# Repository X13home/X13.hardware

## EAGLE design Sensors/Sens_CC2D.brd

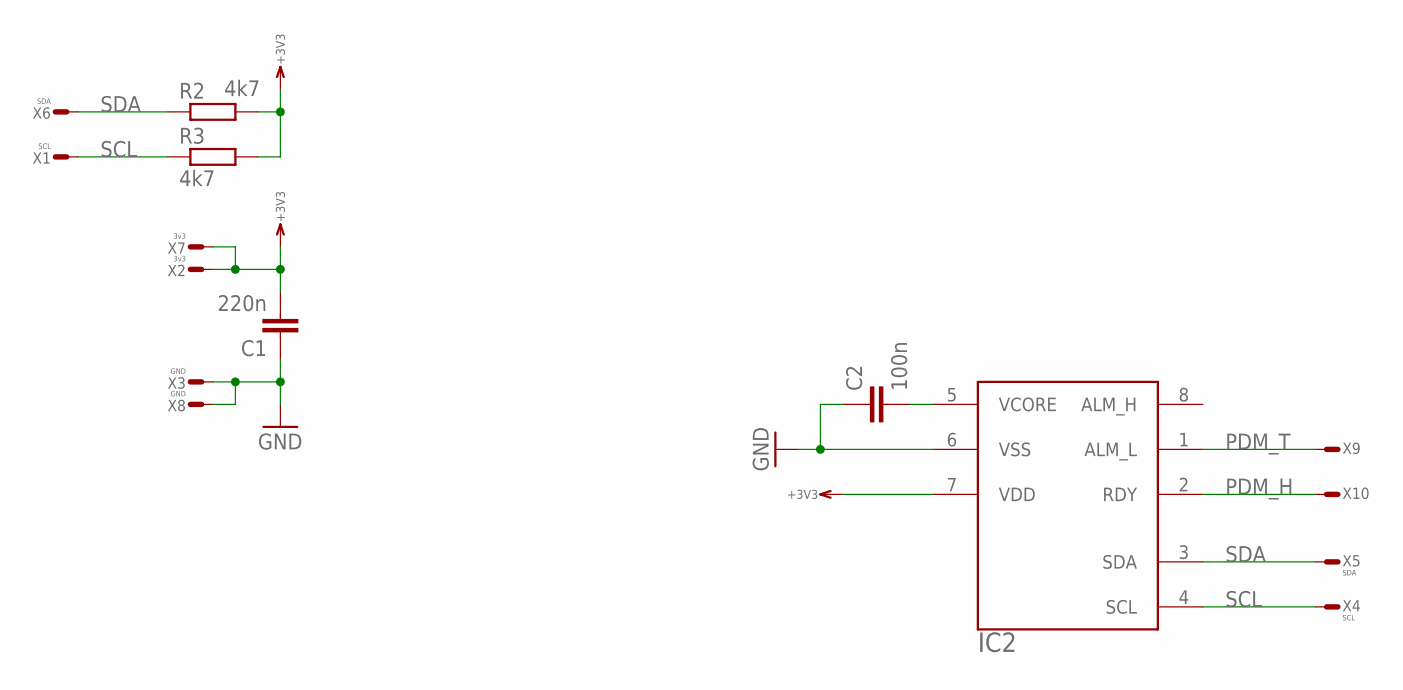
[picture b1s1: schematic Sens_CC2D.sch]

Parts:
C1: 220n; 0603
C2: 100n; 0603
IC2: CC2D
R2, R3: 4k7; 0603
X1, X4: SCL; T1.6/0.9
X2, X7: 3v3; T1.6/0.9
X3, X8: GND; T1.6/0.9
X5, X6: SDA; T1.6/0.9
X9, X10: WIREPADR; S1.27R

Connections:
+3V3: C1.2, IC2.7 (VDD), R2.2, R3.2, X2.1, X7.1
GND: C1.1, C2.1, IC2.6 (VSS), X3.1, X8.1
unnamed: C2.2, IC2.5 (VCORE)
PDM_H: IC2.2 (RDY), X10.1
PDM_T: IC2.1 (ALM_L), X9.1
SCL: IC2.4 (SCL), R3.1, X1.1, X4.1
SDA: IC2.3 (SDA), R2.1, X5.1, X6.1

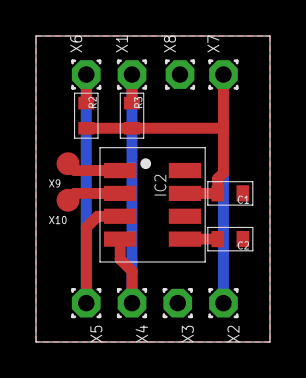
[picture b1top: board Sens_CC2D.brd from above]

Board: 2 copper layers, 13.0 x 17.0 mm, 15 parts (0 on the bottom side), 7 nets.

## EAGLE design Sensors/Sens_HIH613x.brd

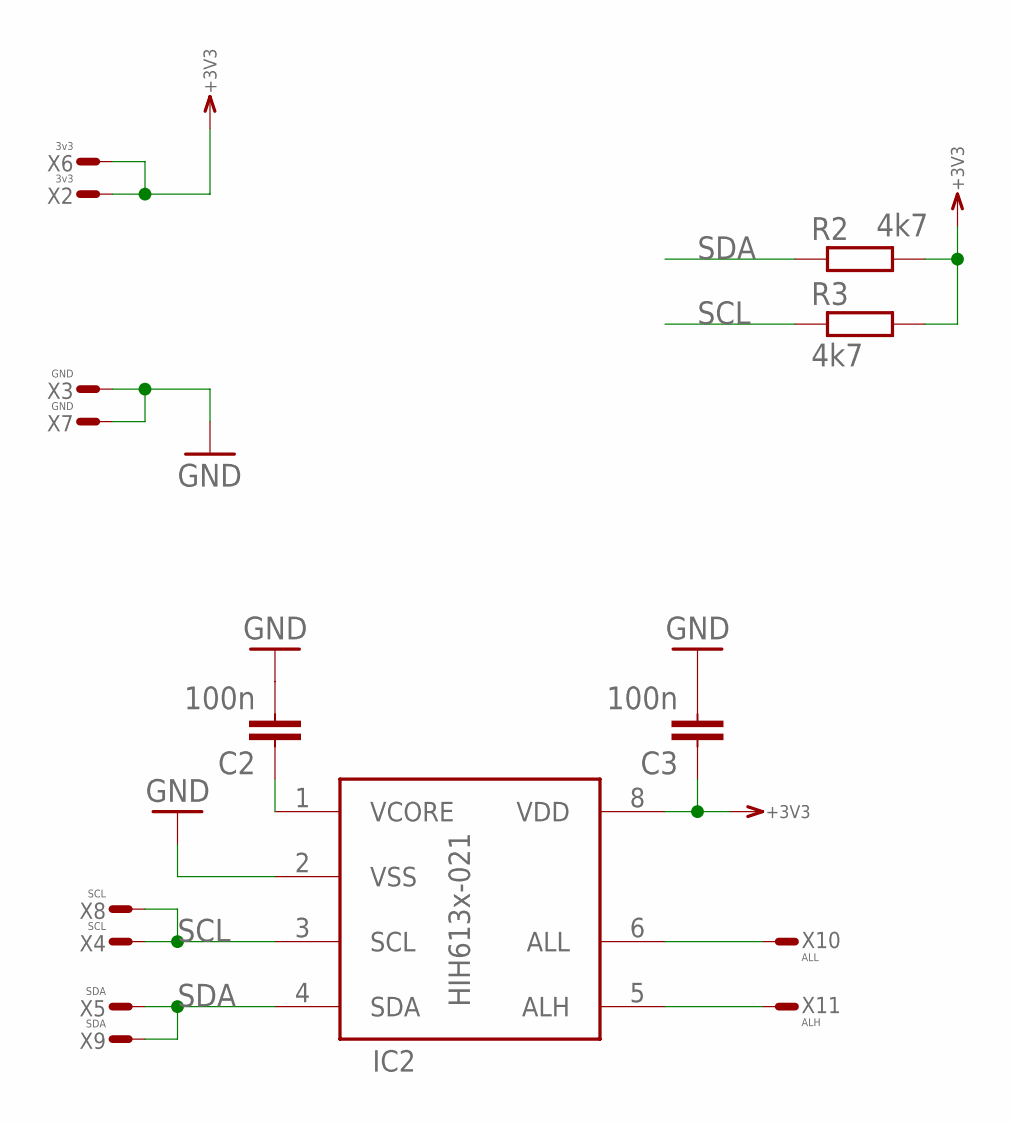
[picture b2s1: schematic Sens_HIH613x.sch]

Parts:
C2, C3: 100n; 0603
IC2: HIH613x-021; SO8
R2, R3: 4k7; 0603
X2, X6: 3v3; T1.6/0.9
X3, X7: GND; T1.6/0.9
X4, X8: SCL; T1.6/0.9
X5, X9: SDA; T1.6/0.9
X10: ALL; S1.27R
X11: ALH; S1.27R

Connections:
+3V3: C3.1, IC2.8 (VDD), R2.2, R3.2, X2.1, X6.1
ALH: IC2.5 (ALH), X11.1
ALL: IC2.6 (ALL), X10.1
GND: C2.2, C3.2, IC2.2 (VSS), X3.1, X7.1
unnamed: C2.1, IC2.1 (VCORE)
SCL: IC2.3 (SCL), R3.1, X4.1, X8.1
SDA: IC2.4 (SDA), R2.1, X5.1, X9.1

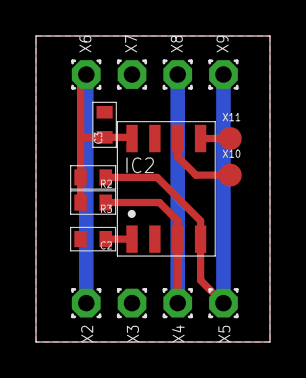
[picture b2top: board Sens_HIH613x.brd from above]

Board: 2 copper layers, 13.0 x 17.0 mm, 15 parts (0 on the bottom side), 7 nets.

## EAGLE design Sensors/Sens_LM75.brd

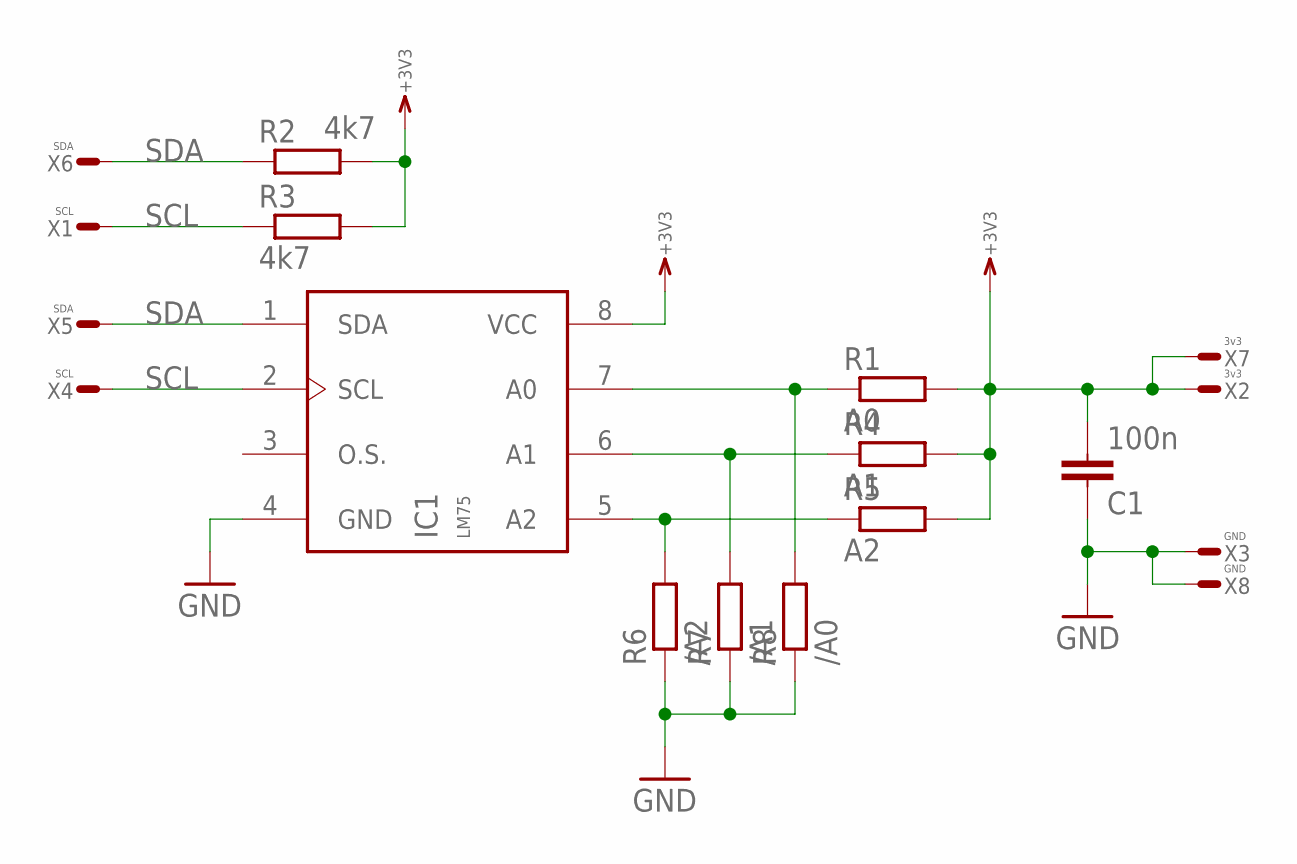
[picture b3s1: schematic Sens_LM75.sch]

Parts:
C1: 100n; 0603
IC1: LM75; SO8
R1: A0; 0603
R2, R3: 4k7; 0603
R4: A1; 0603
R5: A2; 0603
R6: /A2; 0603
R7: /A1; 0603
R8: /A0; 0603
X1, X4: SCL; T1.6/0.9
X2, X7: 3v3; T1.6/0.9
X3, X8: GND; T1.6/0.9
X5, X6: SDA; T1.6/0.9

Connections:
+3V3: C1.2, IC1.8 (VCC), R1.2, R2.2, R3.2, R4.2, R5.2, X2.1, X7.1
GND: C1.1, IC1.4 (GND), R6.1, R7.1, R8.1, X3.1, X8.1
unnamed: IC1.7 (A0), R1.1, R8.2
unnamed: IC1.6 (A1), R4.1, R7.2
unnamed: IC1.5 (A2), R5.1, R6.2
SCL: IC1.2 (SCL), R3.1, X1.1, X4.1
SDA: IC1.1 (SDA), R2.1, X5.1, X6.1

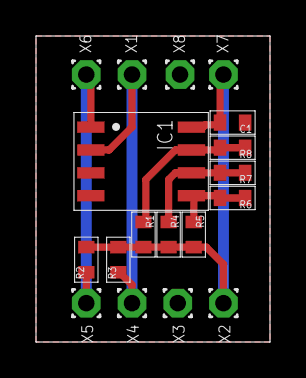
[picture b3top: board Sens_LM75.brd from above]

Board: 2 copper layers, 13.0 x 17.0 mm, 18 parts (0 on the bottom side), 7 nets.

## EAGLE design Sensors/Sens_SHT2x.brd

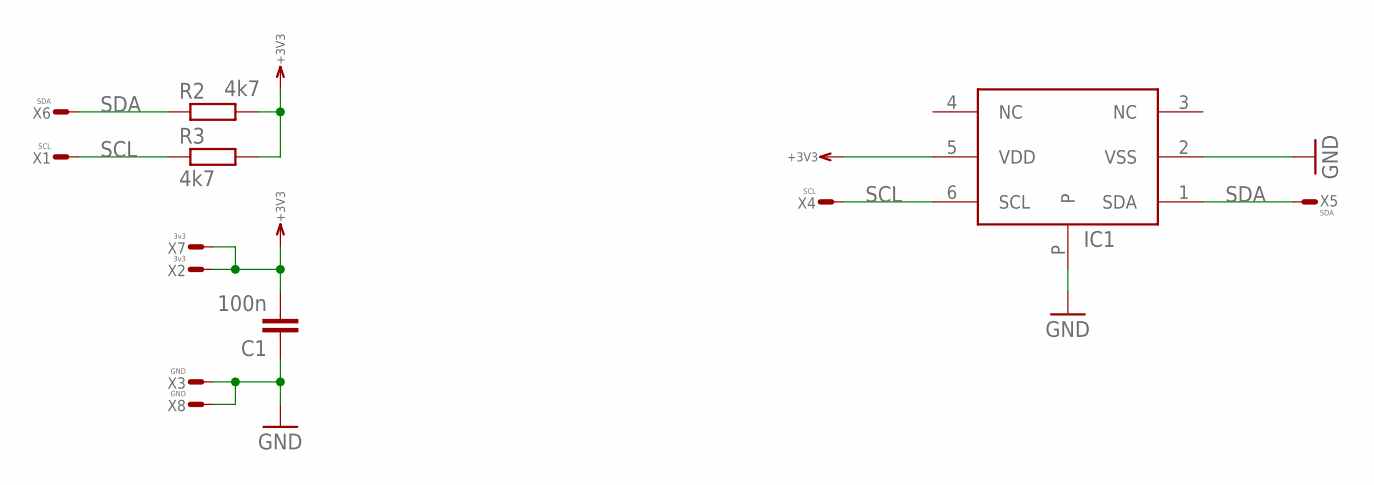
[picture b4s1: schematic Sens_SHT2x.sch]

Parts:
C1: 100n; 0603
IC1: SHT2X; DFN6
R2, R3: 4k7; 0603
X1, X4: SCL; T1.6/0.9
X2, X7: 3v3; T1.6/0.9
X3, X8: GND; T1.6/0.9
X5, X6: SDA; T1.6/0.9

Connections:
+3V3: C1.2, IC1.5 (VDD), R2.2, R3.2, X2.1, X7.1
GND: C1.1, IC1.2 (VSS), IC1.P, X3.1, X8.1
SCL: IC1.6 (SCL), R3.1, X1.1, X4.1
SDA: IC1.1 (SDA), R2.1, X5.1, X6.1

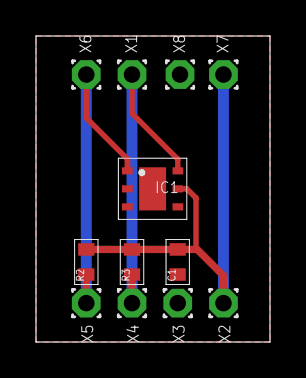
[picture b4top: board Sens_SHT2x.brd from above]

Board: 2 copper layers, 13.0 x 17.0 mm, 12 parts (0 on the bottom side), 4 nets.

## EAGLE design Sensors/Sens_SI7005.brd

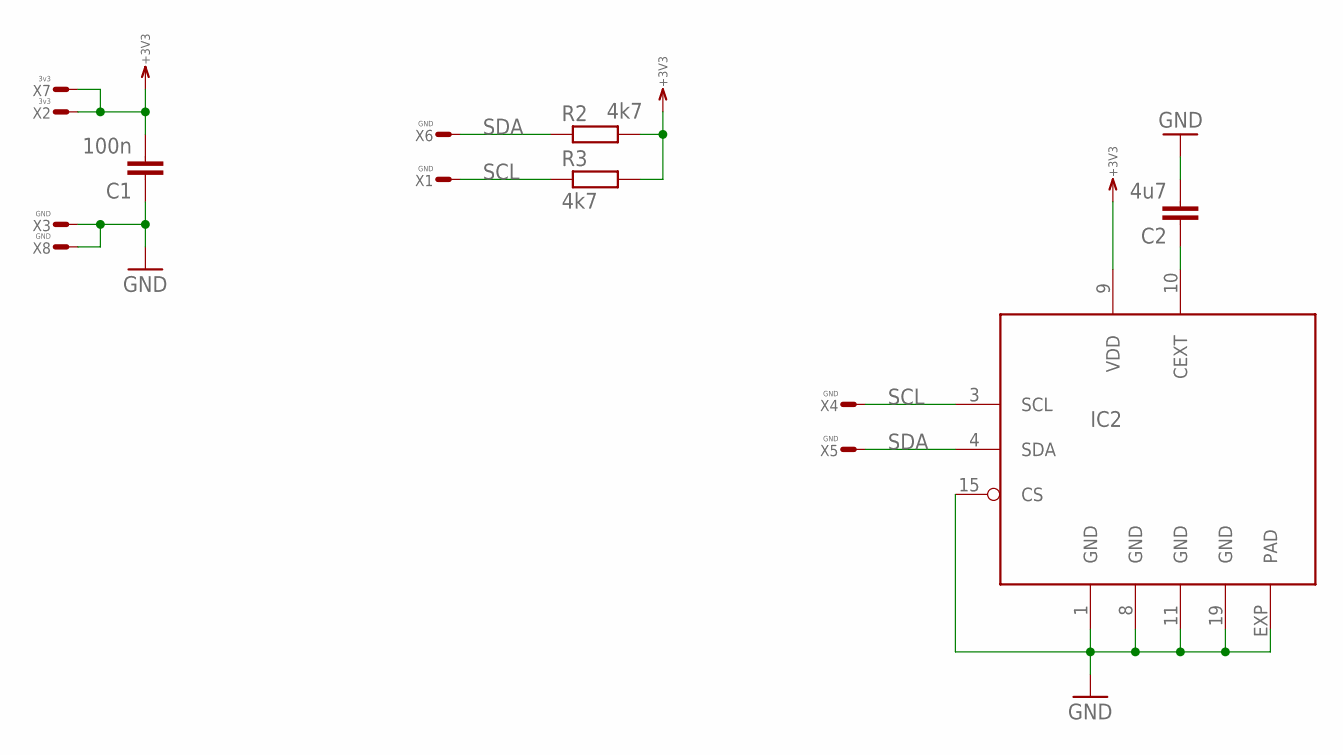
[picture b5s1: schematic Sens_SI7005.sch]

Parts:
C1: 100n; 0603
C2: 4u7; 0603
IC2: SI7005; QFN24
R2, R3: 4k7; 0603
X1, X3, X4, X5, X6, X8: GND; T1.6/0.9
X2, X7: 3v3; T1.6/0.9

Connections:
+3V3: C1.2, IC2.9 (VDD), R2.2, R3.2, X2.1, X7.1
GND: C1.1, C2.2, IC2.1 (GND), IC2.8 (GND), IC2.11 (GND), IC2.15 (CS), IC2.19 (GND), IC2.EXP (PAD), X3.1, X8.1
unnamed: C2.1, IC2.10 (CEXT)
SCL: IC2.3 (SCL), R3.1, X1.1, X4.1
SDA: IC2.4 (SDA), R2.1, X5.1, X6.1

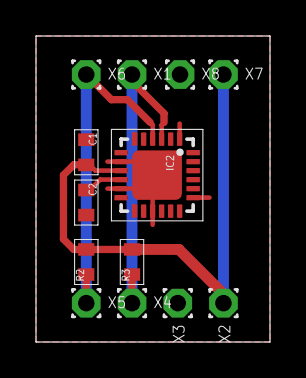
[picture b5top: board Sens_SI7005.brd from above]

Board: 2 copper layers, 13.0 x 17.0 mm, 13 parts (0 on the bottom side), 5 nets.
